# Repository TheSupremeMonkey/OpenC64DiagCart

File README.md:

# UNTESTED PLEASE DON'T USE THE GERBERS YET!

# OpenC64DiagCart
OpenC64DiagCart started as a fork of OpenC64Cart by SukkoPera [available at](https://github.com/SukkoPera/OpenC64Cart). The primary goal being to replace all the jumpers with a single rotary DIP switch while also retaining the ability to have one of the 8 image slots be used as a C64 Dead Test. 

### Summary
Most Commodore 64 diagnostic cartriges are a standard 8k image, the exception being the dead that has to be run in Ultimax mode. To keep the design simple and make it easy to prototype, I decided to use parts I already had. In the end I ended up using a 74LS02 quad 2-input NOR gate and a 4066 quad bilateral switch, which are both spare parts I keep around for reparing Commdoe 64 motherboards. The 74LS02 is used to read the state of the DIP switch which is tied to the last 3 address pins (A13,A14, & A15) of the 27512. When all 3 pins are low the CE and OE pins on the 27512 are connected through a switch in 4066 to ROMH and GAME is set high. For any other combination of A13, A14, and A15 CE and OE are connected through a different switch on the 4066 to ROML and EXROM is set high. This means that the first image out of 8 on the 27512 ROM will automatically be in Ultimax mode and can run a dead test. All the other images can be any 8k cartridge image you want. 
 
 I also added an RGB LED to give a visual queue as to which image is selected. THe RGB is also tied to the dip switch so that meant that when all three addresses are low the LED will be off. I added a 2nd LED that is triggered when Utilimax mode is on, this way the dead test always gets a special light. 
 
### Configuration

|Slot	|Image								|RGB	|LED	|A13 (B)	|A14 (G)	|A15 (R)	|MODE|
|-------|-----------------------------------|-------|-------|-----------|-----------|-----------|----|
|0		|Dead Test Rev 781220				|OFF	|ON		|0			|0			|0			|Dead Test|
|1		|C-64 Diagnostic Rev 586220*		|Blue	|OFF	|1			|0			|0			|Normal|
|2		|Roßmöller Doctor64					|Green	|OFF	|0			|1			|0			|Normal|
|3		|Trilogic 64 Doctor					|Cyan	|OFF	|1			|1			|0			|Normal|
|4		|C64 Burn In “Final Rev 3.0”		|Red	|OFF	|0			|0			|1			|Normal|
|5		|1541 Diagnostic					|Purple	|OFF	|1			|0			|1			|Normal|
|6		|PSID64 Sid Player					|Yellow	|OFF	|0			|1			|1			|Normal|
|7		|C-64 Diagnostic Rev 586220-SWINSID	|White	|OFF	|1			|1			|1			|Normal|

### Thanks
While this is technically a fork of [OpenC64Cart](https://github.com/SukkoPera/OpenC64Cart), it was also very helpful to look at the design of Bwack's [Vers64Cart](https://github.com/bwack/Versa64Cart). A ton of credit also needs to go to the [World Of Jani](http://blog.worldofjani.com/) blog for both the [diagnostic images](http://blog.worldofjani.com/?p=164) and [code](http://blog.worldofjani.com/?p=1981), as well a ton of [documentation](http://blog.worldofjani.com/?p=879) on how these cartridges work.

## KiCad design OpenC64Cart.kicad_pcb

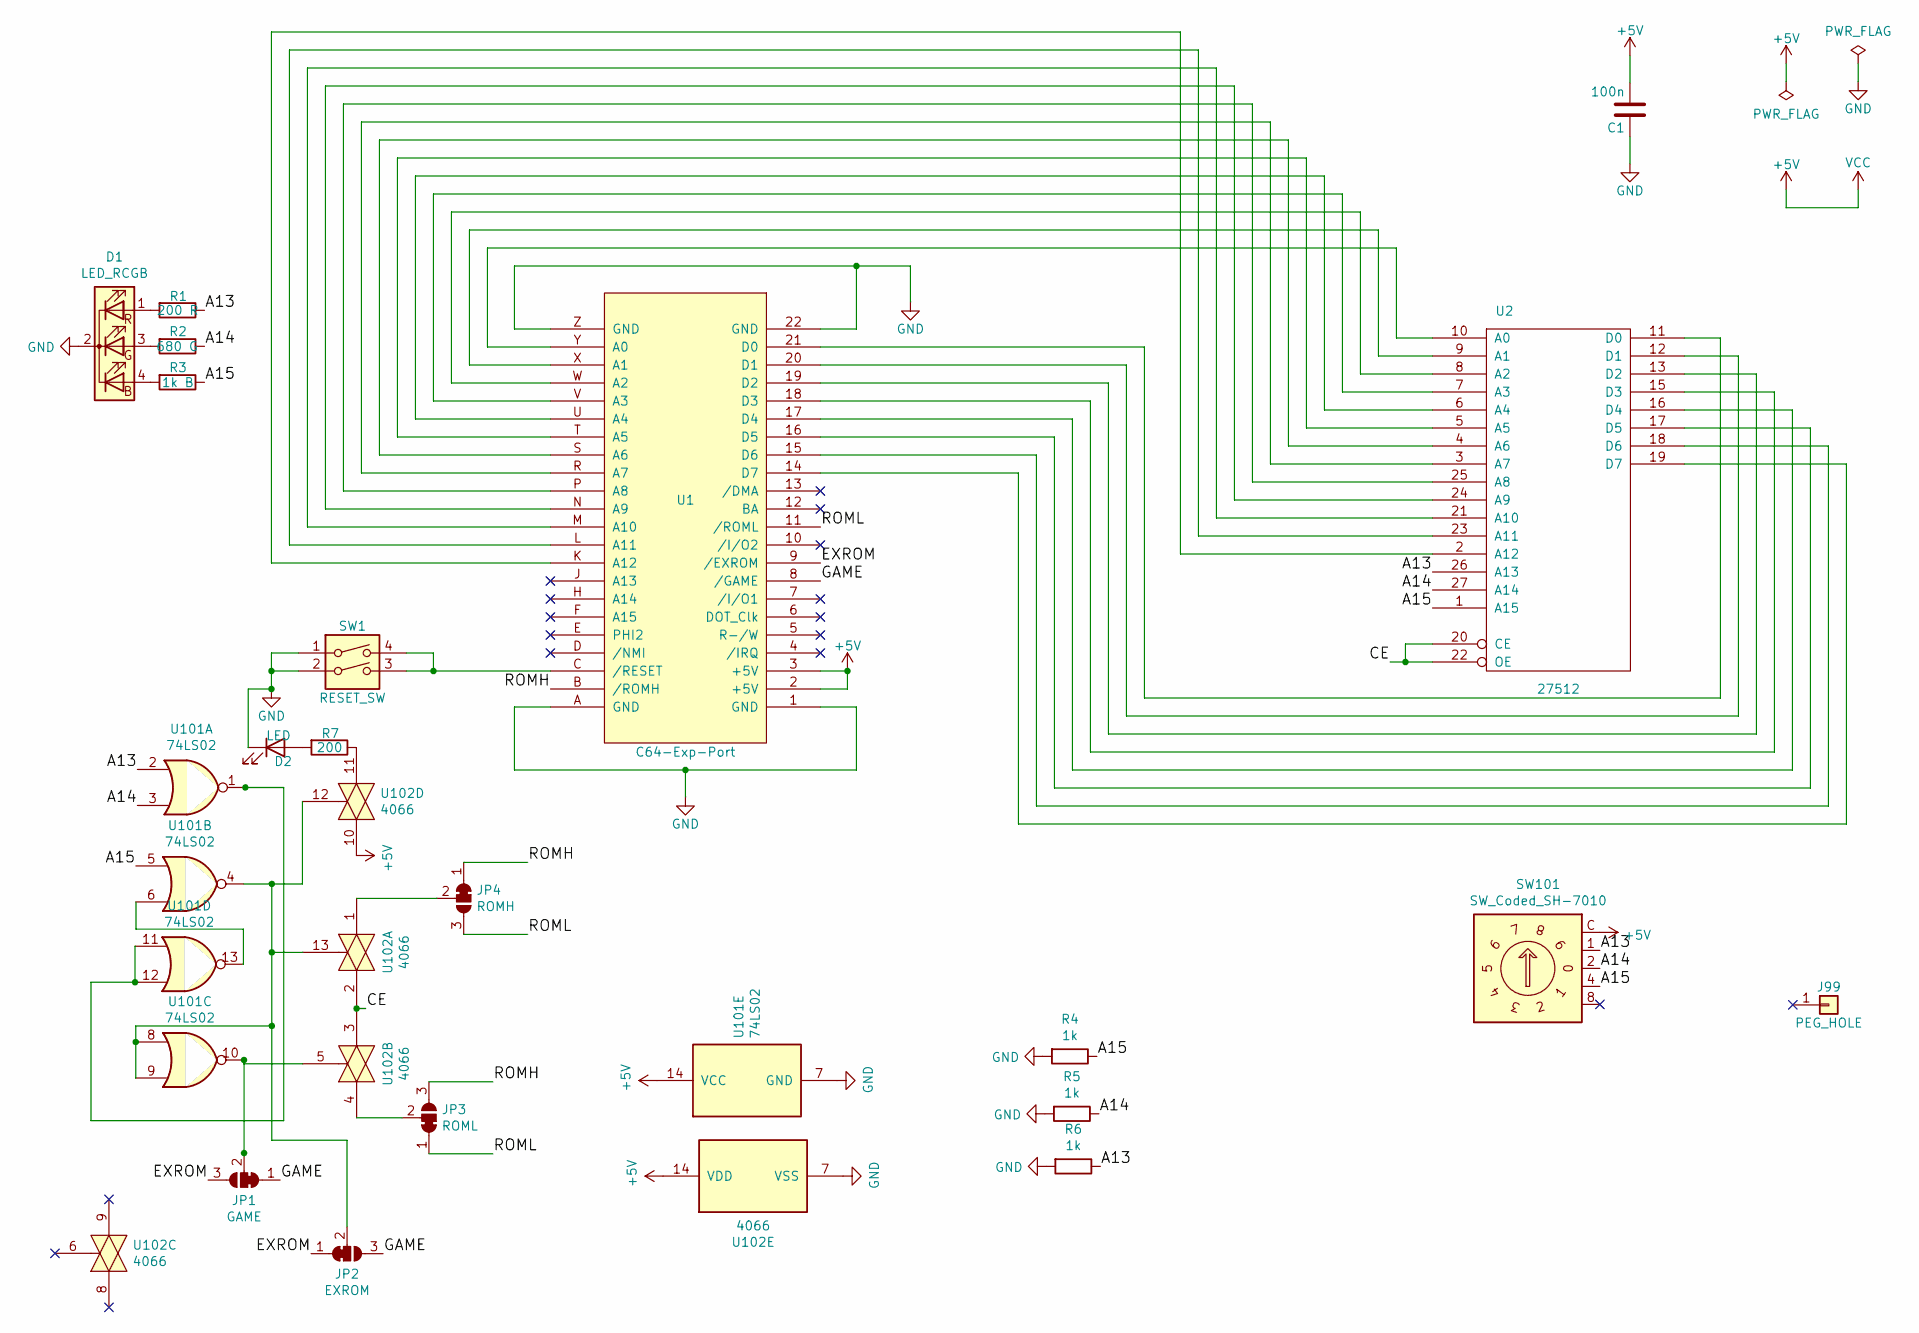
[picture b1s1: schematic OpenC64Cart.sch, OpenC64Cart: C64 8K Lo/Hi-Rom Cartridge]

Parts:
C1: 100n; C_0805+THT
D1: LED_RCGB; LED_D5.0mm-4_RGB
D2: LED; LED_D5.0mm
J99: PEG_HOLE; C64_PEG_HOLE
JP1: GAME; SolderJumper-3_P1.3mm_Bridged12_RoundedPad1.0x1.5mm_NumberL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
JP2: EXROM; SolderJumper-3_P1.3mm_Bridged12_RoundedPad1.0x1.5mm_NumberL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
JP3: ROML; SolderJumper-3_P1.3mm_Bridged12_RoundedPad1.0x1.5mm_NumberL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
JP4: ROMH; SolderJumper-3_P1.3mm_Bridged12_RoundedPad1.0x1.5mm_NumberL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
R1: 200 R; R_Axial_DIN0207_L6.3mm_D2.5mm_P7.62mm_Horizontal
R2: 680 G; R_Axial_DIN0207_L6.3mm_D2.5mm_P7.62mm_Horizontal
R3: 1k B; R_Axial_DIN0207_L6.3mm_D2.5mm_P7.62mm_Horizontal
R4, R5, R6: 1k; R_Axial_DIN0207_L6.3mm_D2.5mm_P7.62mm_Horizontal
R7: 200; R_Axial_DIN0207_L6.3mm_D2.5mm_P7.62mm_Horizontal
SW1: RESET_SW; PCB_PUSH
SW101: SW_Coded_SH-7010; SW_DIP4-ROTARY-BCD-8or10
U1: C64-Exp-Port; C64-Cart
U2: 27512; dil_28-600_socket
U101: 74LS02; DIP-14_W7.62mm
U102: 4066; DIP-14_W7.62mm

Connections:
+5V: C1.2, SW101.C, U1.2 (+5V), U1.3 (+5V), U2.28 (VCC), U101.14 (VCC), U102.10, U102.14 (VDD)
/A13: R1.1, R6.1, SW101.1, U2.26 (A13), U101.2
/A14: R2.1, R5.1, SW101.2, U2.27 (A14), U101.3
/A15: R3.1, R4.1, SW101.4, U2.1 (A15), U101.5
/CE: U2.20 (CE), U2.22 (OE), U102.2, U102.3
/EXROM: JP1.3 (B), JP2.1 (A), U1.9 (/EXROM)
/GAME: JP1.1 (A), JP2.3 (B), U1.8 (/GAME)
/ROMH: JP3.3 (B), JP4.1 (A), U1.B (/ROMH)
/ROML: JP3.1 (A), JP4.3 (B), U1.11 (/ROML)
GND: C1.1, D1.2 (K), D2.1 (K), R4.2, R5.2, R6.2, SW1.1, SW1.2, U1.1 (GND), U1.22 (GND), U1.A (GND), U1.Z (GND), U2.14 (GND), U101.7 (GND), U102.7 (VSS)
unnamed: D1.1 (RA), R1.2
unnamed: D1.3 (GA), R2.2
unnamed: D1.4 (BA), R3.2
unnamed: D2.2 (A), R7.2
unnamed: JP1.2 (C), U101.10, U102.5
unnamed: JP2.2 (C), U101.4, U101.8, U101.9, U102.12, U102.13
unnamed: JP3.2 (C), U102.4
unnamed: JP4.2 (C), U102.1
unnamed: R7.1, U102.11
unnamed: SW1.3, SW1.4, U1.C (/RESET)
unnamed: U1.14 (D7), U2.19 (D7)
unnamed: U1.15 (D6), U2.18 (D6)
unnamed: U1.16 (D5), U2.17 (D5)
unnamed: U1.17 (D4), U2.16 (D4)
unnamed: U1.18 (D3), U2.15 (D3)
unnamed: U1.19 (D2), U2.13 (D2)
unnamed: U1.20 (D1), U2.12 (D1)
unnamed: U1.21 (D0), U2.11 (D0)
unnamed: U1.K (A12), U2.2 (A12)
unnamed: U1.L (A11), U2.23 (A11)
unnamed: U1.M (A10), U2.21 (A10)
unnamed: U1.N (A9), U2.24 (A9)
unnamed: U1.P (A8), U2.25 (A8)
unnamed: U1.R (A7), U2.3 (A7)
unnamed: U1.S (A6), U2.4 (A6)
unnamed: U1.T (A5), U2.5 (A5)
unnamed: U1.U (A4), U2.6 (A4)
unnamed: U1.V (A3), U2.7 (A3)
unnamed: U1.W (A2), U2.8 (A2)
unnamed: U1.X (A1), U2.9 (A1)
unnamed: U1.Y (A0), U2.10 (A0)
unnamed: U101.1, U101.11, U101.12
unnamed: U101.6, U101.13

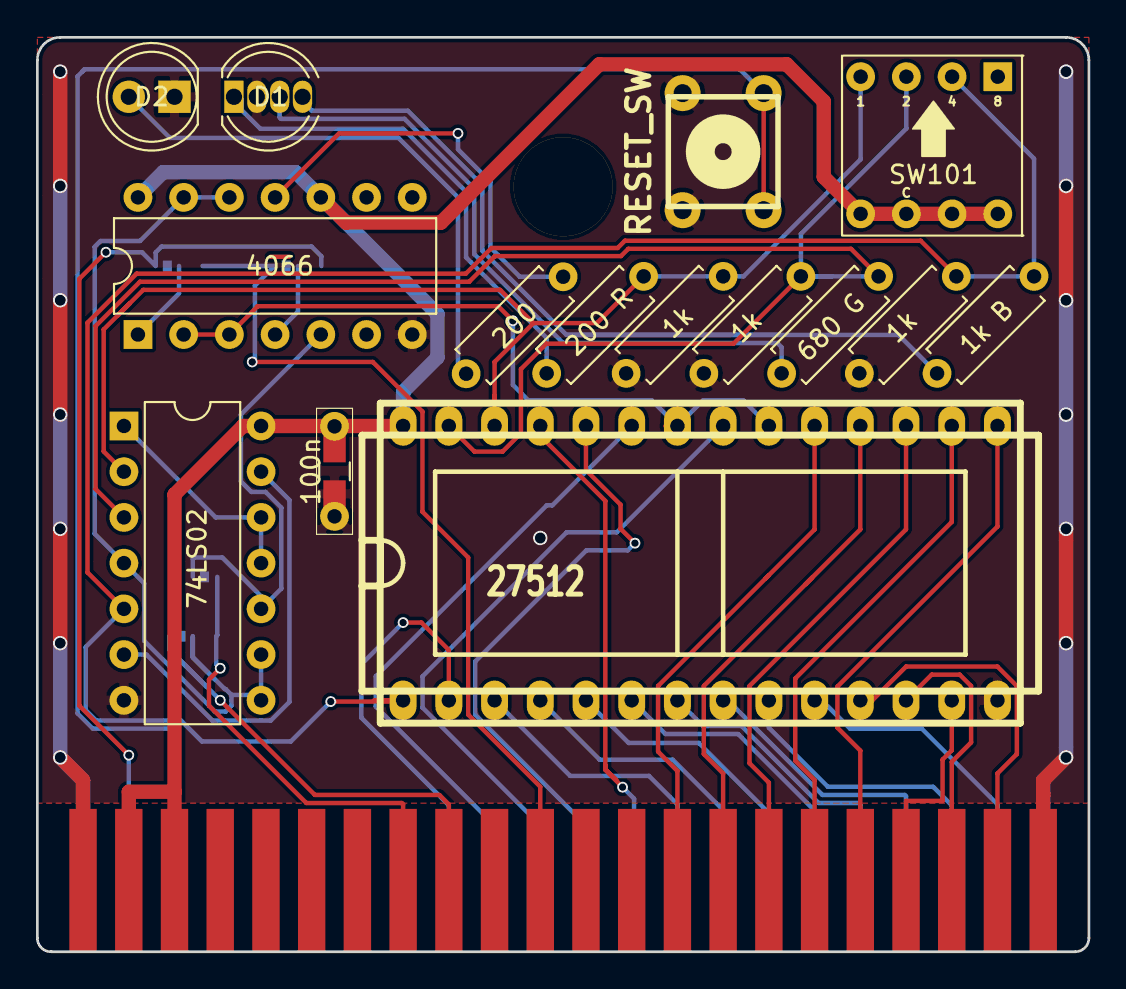
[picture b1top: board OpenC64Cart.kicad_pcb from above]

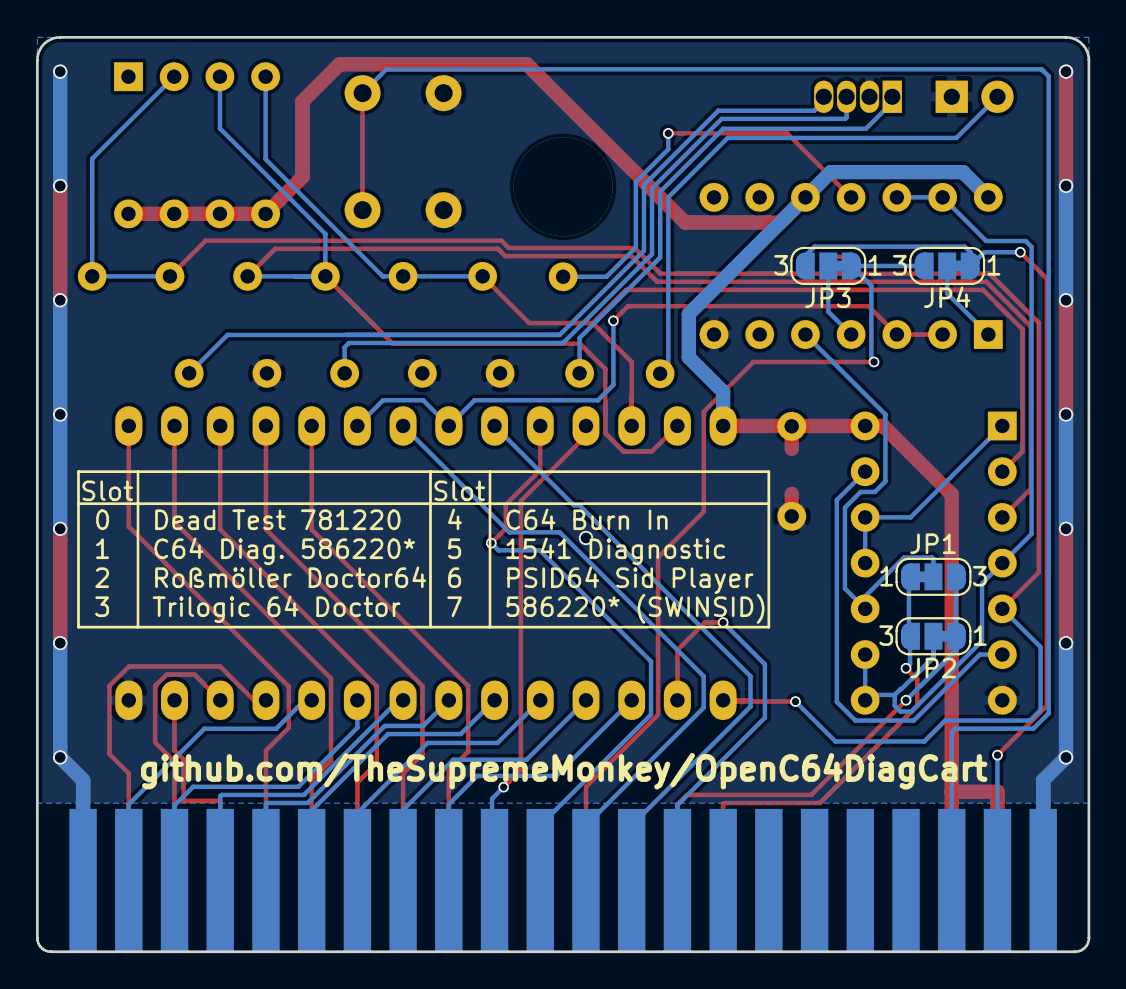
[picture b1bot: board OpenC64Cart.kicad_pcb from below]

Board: 2 copper layers, 58.4 x 50.8 mm, 21 parts (4 on the bottom side), 43 nets.

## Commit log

2021-11-24 OpenC64DiagCart
    Initial commit of OpenC64DiagCart fork.
2021-11-24 PCB Render Update
2021-12-15 Fixed Everything
    This is still untested beta. I had a bunch of things wrong on my first test PCBs.
2021-12-22 Tested
    Finally received the latest revision PCB and everything is now working. I tweaked the LED resistors for the RGB LEDs I have but they may need tweaked depending on the actual specs of the LED used.
